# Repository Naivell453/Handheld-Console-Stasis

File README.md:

# Handheld-Console-Stasis
A handheld console that has it's own OS, Model and Games (Stasis 2026 Project)

Hardware

The console is built around the Orange Pi Zero 2W (Allwinner H618, quad-core Cortex-A53, 1.5GB RAM). It features a 3.5" ILI9488 SPI display, stereo audio through two MAX98357A I2S amplifiers driving 4Ω 3W speakers, a 5000mAh LiPo battery with USB-C charging, and an MPU-6050 gyroscope for motion controls. Input is handled by 8 tactile push buttons arranged in a GBA-style layout.

Firmware

Built with Buildroot targeting the Orange Pi Zero 3 defconfig, which is compatible with the Zero 2W as both use the Allwinner H618 SoC.
To build:
bashgit clone https://github.com/buildroot/buildroot
cd buildroot
make orangepi_zero3_defconfig
make -j1
Flash output/images/sdcard.img to an SD card using Balena Etcher. The game launches automatically on boot with no password required.

Games

Ball Maze is a 2D physics-based maze game where the gyroscope controls the gravity direction. Rotating the console changes which way the ball falls, and the objective is to guide the ball out of the maze.
Platformer is a 2D side-scrolling platformer controlled with the D-pad and buttons.
FPS is a 3D first-person shooter with gyroscope-assisted aiming, currently in development.

PCB

Designed in EasyEDA and manufactured by JLCPCB. 2-layer through-hole design at 200mm × 90mm. The screen connects via SPI, the gyroscope via I2C, audio via I2S, and all buttons via GPIO pins on the Orange Pi header. Power is provided through an MT3608 boost converter stepping the battery voltage up to 5V.

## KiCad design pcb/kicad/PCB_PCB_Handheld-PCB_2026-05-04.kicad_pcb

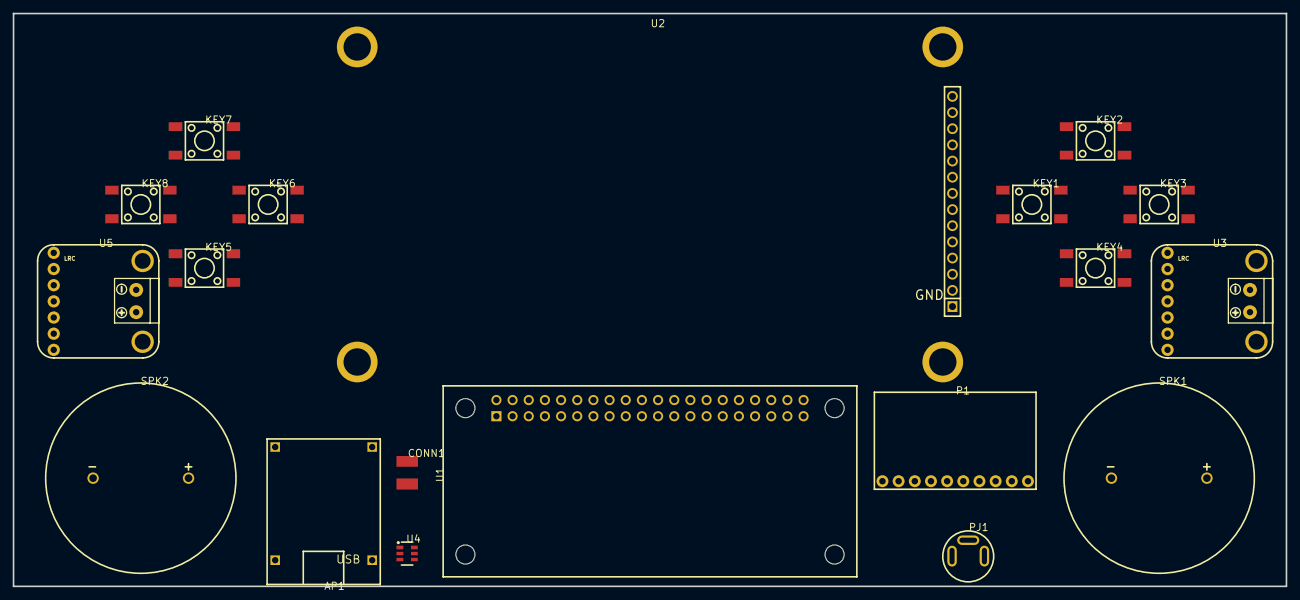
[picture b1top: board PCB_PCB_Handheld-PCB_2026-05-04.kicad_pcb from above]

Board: 2 copper layers, 200.0 x 90.0 mm, 19 parts (0 on the bottom side), 26 nets, no tracks yet.

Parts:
AP1: TP4056 CHARGING MODDULE; TP4056-CHARGING-MODULE_TP4056
CONN1: CONN_01x02; CONN_01X02_SMD
KEY1, KEY2, KEY3, KEY4, KEY5, KEY6, KEY7, KEY8: 4PINTACTPCBTHTPUSHBUTTON; SW-SMD_4P-L6.0-W6.0-P4.50-LS10.0_TL3301EF160QG
P1: MPU6050
PJ1: PJ-3920-3A; AUDIO-TH_PJ-3920-3A
SPK1, SPK2: AST-03008MR-R; BEEP-TH_BD29.9-P15.00
U1: ORANGE-PI-ZERO-2W; COMM-TH_40P-L65.0-W30.0-P2.54_ORANGE-PI-ZERO-2W
U2: 3.5inch ILI9488 Display; 3.5INCH ILI9488
U3, U5: MAX98357A
U4: MT3608

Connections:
3V3: P1.1, U1.1, U1.17, U2.1, U2.8
5V: U1.2, U1.4, U3.1, U4.6, U5.1
12S_LRCK: U3.7, U5.7
BAT_P: AP1.1, CONN1.1
BTN_B: KEY1.1, U1.18
BTN_DOWN: KEY5.1, U1.26
BTN_LEFT: KEY8.1, U1.13
BTN_RIGHT: KEY6.1, U1.15, U1.16
BTN_SELECT: KEY4.1, U1.31
BTN_START: KEY3.1, U1.29
BTN_UP: KEY7.1, U1.7
GND: AP1.2, CONN1.2, KEY1.2, KEY2.2, KEY3.2, KEY4.2, KEY5.2, KEY6.2, KEY7.2, KEY8.2, P1.2, PJ1.1, U1.6, U1.9, U1.14, U1.20, U1.25, U1.30, U1.34, U1.39, U2.2, U3.2, U4.2, U5.2
I2C_SCL: P1.3, U1.5
I2C_SDA: P1.4, U1.3
I2S_BCLK: U1.12, U3.6, U5.6
I2S_DIN: U1.38, U3.5, U5.5
LCD_DC: U1.22, U2.5
LCD_RST: U1.11, U2.4
SPI_CS: U1.24, U2.3
SPI_MISO: U1.21, U2.9
SPI_MOSI: U1.19, U2.6
SPI_SCK: U1.23, U2.7
SPKR_L_N: SPK2.2, U5.8
SPKR_L_P: PJ1.3, SPK2.1, U5.9
SPKR_R_N: SPK1.2, U3.8
SPKR_R_P: PJ1.2, SPK1.1, U3.9

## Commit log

2026-05-04 Added PCB
2026-05-04 Created pcb folder
2026-05-04 Created pcb folder gerber
2026-05-04 Added gerber pcb files
2026-05-04 Added EasyEDA .json
2026-05-04 Created kicad folder
2026-05-04 Added Kicad PCB
2026-05-04 Create orangepi_zero3_defconfig
